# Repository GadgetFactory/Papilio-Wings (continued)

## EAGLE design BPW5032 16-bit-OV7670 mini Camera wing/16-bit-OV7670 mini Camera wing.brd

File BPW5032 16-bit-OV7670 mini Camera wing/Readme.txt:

BPW5032 OV7670 Camera Wing Manufacturing Package - Current Version 1.0

Special assembly instructions:
-Use RED for the PCB color.

CHANGELOG
8/22/2014 Version 1.0

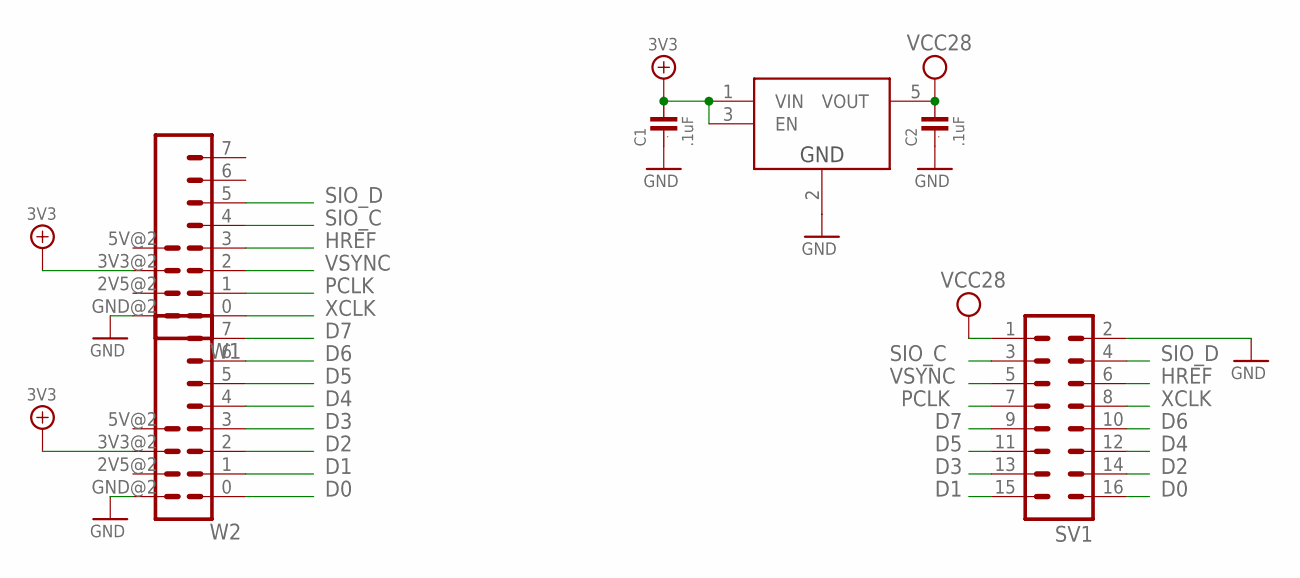
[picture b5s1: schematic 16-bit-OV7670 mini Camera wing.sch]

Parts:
C1, C2: .1uF; 0603; PARTNO GRM188F51E104ZA01D
SV1: ML16; PARTNO PRPC004DAAN-RC
U1: TPS73028; SOT23-DBV; PARTNO TPS73028DBVT
W1, W2: WING8WING8_NOHOLES; WINGSIDE_8BIT_NOHOLES; PARTNO 68001-112HLF

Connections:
3V3: C1.2, U1.1 (VIN), U1.3 (EN), W1.3V3@2 (3V3), W2.3V3@2 (3V3)
D0: SV1.16, W2.0 (1)
D1: SV1.15, W2.1 (2)
D2: SV1.14, W2.2 (3)
D3: SV1.13, W2.3 (4)
D4: SV1.12, W2.4 (5)
D5: SV1.11, W2.5 (6)
D6: SV1.10, W2.6 (7)
D7: SV1.9, W2.7 (8)
GND: C1.1, C2.1, SV1.2, U1.2 (GND), W1.GND@2 (GND), W2.GND@2 (GND)
HREF: SV1.6, W1.3 (4)
PCLK: SV1.7, W1.1 (2)
SIO_C: SV1.3, W1.4 (5)
SIO_D: SV1.4, W1.5 (6)
VCC28: C2.2, SV1.1, U1.5 (VOUT)
VSYNC: SV1.5, W1.2 (3)
XCLK: SV1.8, W1.0 (1)

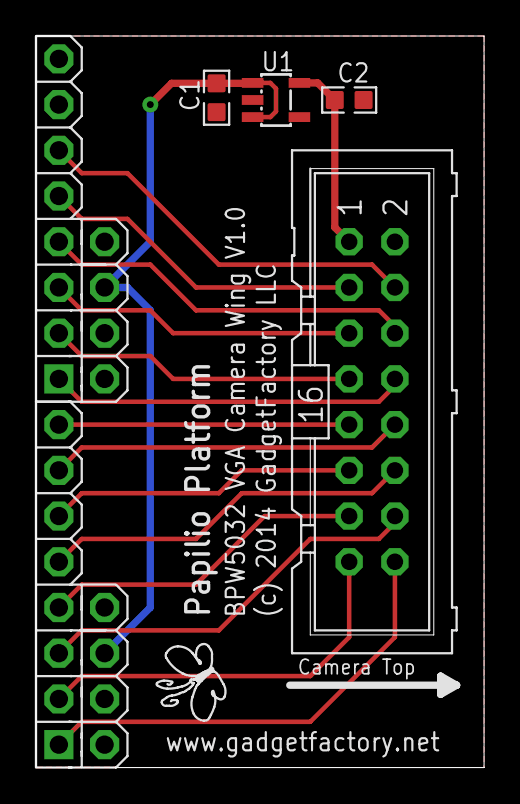
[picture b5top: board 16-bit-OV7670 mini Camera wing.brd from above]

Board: 2 copper layers, 24.9 x 40.6 mm, 7 parts (0 on the bottom side), 17 nets.

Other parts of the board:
U$1: BUTTERFLY_LOGO

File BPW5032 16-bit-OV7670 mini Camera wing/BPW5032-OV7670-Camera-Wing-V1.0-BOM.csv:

Qty-1,Part References,Value,Package,Mfg Part Num,Mfg Name,VID,Vendor Part Num,Description,Pkg Code,XREF
1,"SV1",,ML16,PRPC004DAAN-RC,Sullins Connector,DK,S2011EC-04-ND,CONN HEADER .100"" DUAL STR 8POS,ML16,REF194
2,"C1, C2",.1uF,0603,GRM188F51E104ZA01D,MURATA ELECTRONICS (VA),DK,490-1575-1-ND,CAP CER .1UF 25V Y5V 0603,603,REF96
1,"U1",TPS73028,SOT23-DBV,TPS73028DBVT,Texas Instruments,DK,296-18063-1-ND,IC REG LDO 2.8V 0.2A SOT23-5,SOT23-DBV,REF195
2,"W1, W2",WING8WING8_NOHOLES,WINGSIDE_8BIT_NOHOLES,68001-112HLF,FCI,DK,609-3275-ND,Papilio 8-bit Wing header. 12 Male Pin Headers to be split into 8 pins and 4 pins.,WINGSIDE_8BIT_NOHOLES,REF193

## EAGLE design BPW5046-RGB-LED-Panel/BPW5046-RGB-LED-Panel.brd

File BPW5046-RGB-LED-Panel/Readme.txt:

BPW5046 RGB LED Panel Wing Manufacturing Package - Current Version 1.1

Special assembly instructions:
-Use RED for the PCB color.

CHANGELOG
8/21/2014 Version 1.1

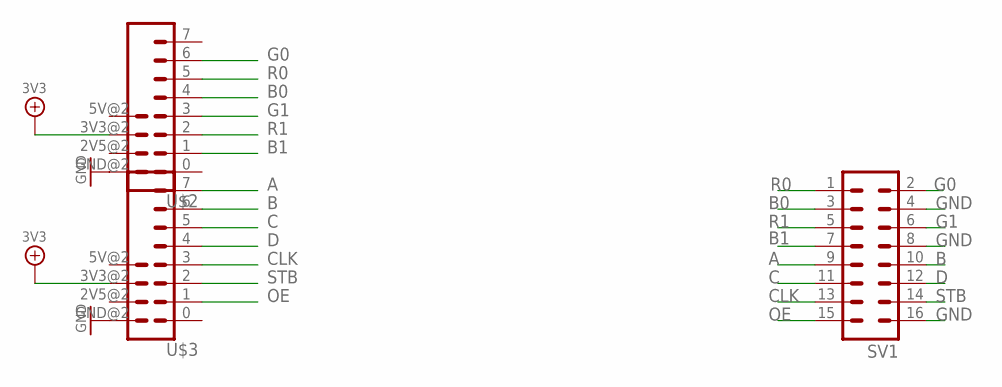
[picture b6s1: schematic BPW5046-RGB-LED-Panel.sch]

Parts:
SV1: ML16; PARTNO PRPC004DAAN-RC
U$2, U$3: WING8WING8_NOHOLES; WINGSIDE_8BIT_NOHOLES; PARTNO 68001-112HLF

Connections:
3V3: U$2.3V3@2 (3V3), U$3.3V3@2 (3V3)
A: SV1.9, U$3.7 (8)
B: SV1.10, U$3.6 (7)
B0: SV1.3, U$2.4 (5)
B1: SV1.7, U$2.1 (2)
C: SV1.11, U$3.5 (6)
CLK: SV1.13, U$3.3 (4)
D: SV1.12, U$3.4 (5)
G0: SV1.2, U$2.6 (7)
G1: SV1.6, U$2.3 (4)
GND: SV1.4, SV1.8, SV1.16, U$2.GND@2 (GND), U$3.GND@2 (GND)
OE: SV1.15, U$3.1 (2)
R0: SV1.1, U$2.5 (6)
R1: SV1.5, U$2.2 (3)
STB: SV1.14, U$3.2 (3)

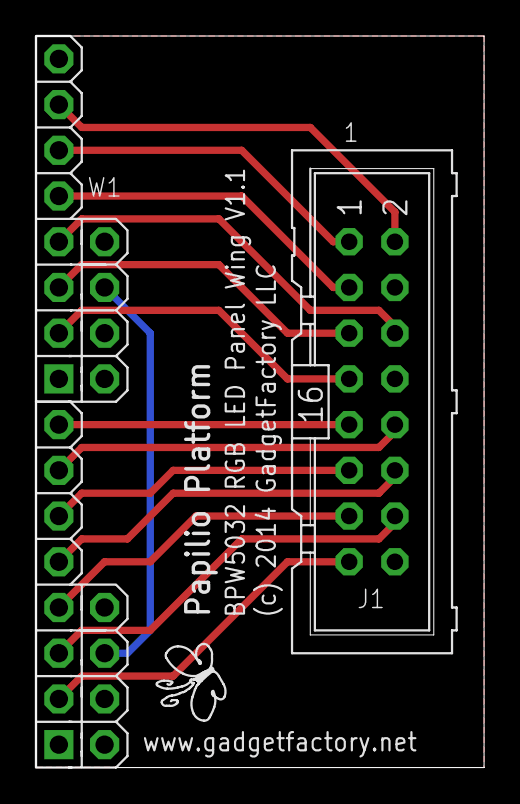
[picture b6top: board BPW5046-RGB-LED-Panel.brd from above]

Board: 2 copper layers, 24.9 x 40.6 mm, 4 parts (0 on the bottom side), 15 nets.

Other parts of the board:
U$1: BUTTERFLY_LOGO

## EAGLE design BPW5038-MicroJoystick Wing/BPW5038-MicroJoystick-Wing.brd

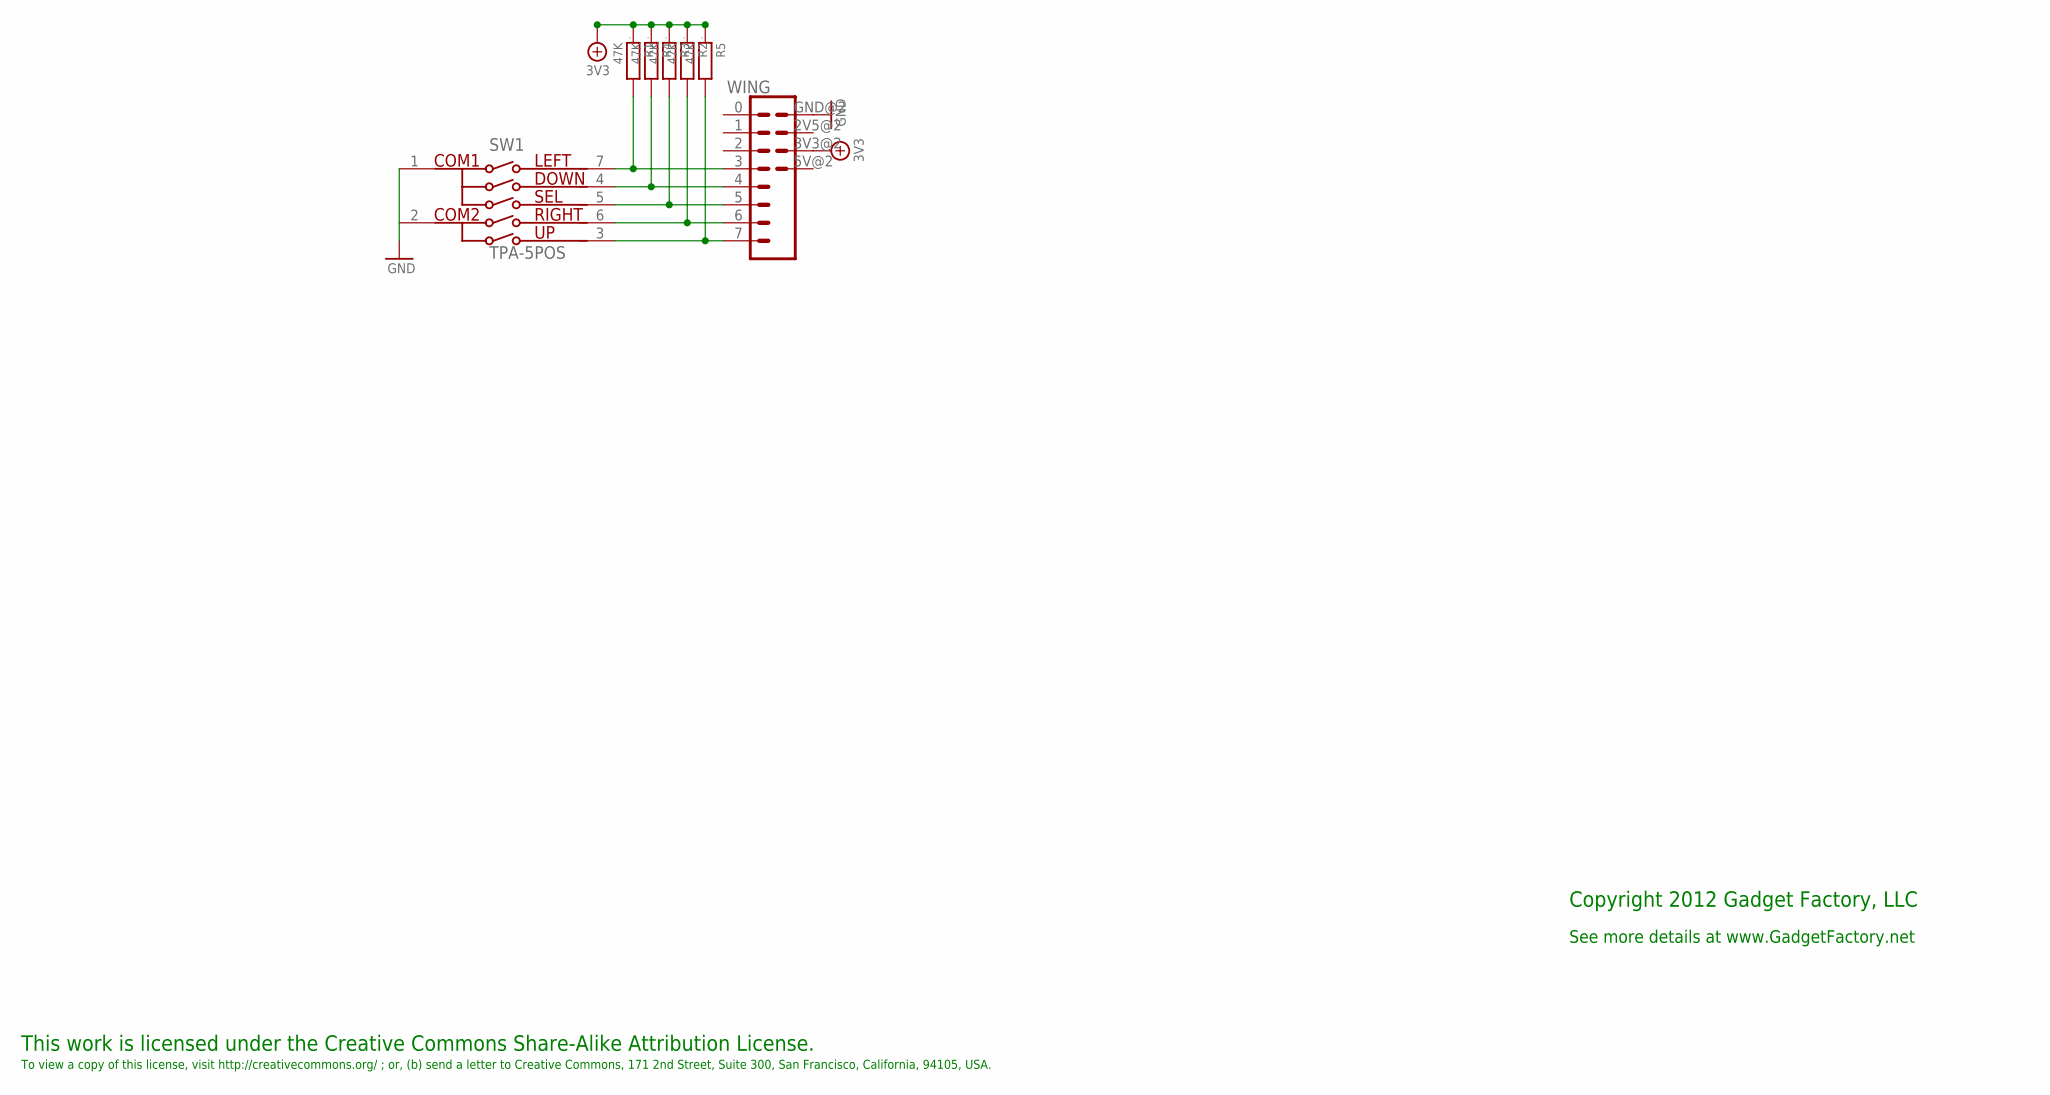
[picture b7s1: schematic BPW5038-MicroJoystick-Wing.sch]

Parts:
LOGO1: BUTTERFLY_LOGO
R1, R2, R3, R4, R5: 47K; 0603
SW1: TPA-5POS
WING: WING8; WINGSIDE_8BIT

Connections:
3V3: R1.1, R2.1, R3.1, R4.1, R5.1, WING.3V3@2 (3V3)
GND: SW1.1 (COM1), SW1.2 (COM2), WING.GND@2 (GND)
unnamed: R4.2, SW1.4 (DOWN), WING.4 (5)
unnamed: R1.2, SW1.7 (LEFT), WING.3 (4)
unnamed: R2.2, SW1.6 (RIGHT), WING.6 (7)
unnamed: R3.2, SW1.5 (SELECT), WING.5 (6)
unnamed: R5.2, SW1.3 (UP), WING.7 (8)

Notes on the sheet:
This work is licensed under the Creative Commons Share-Alike Attribution License.
To view a copy of this license, visit http://creativecommons.org/ ; or, (b) send a letter to Creative Commons, 171 2nd Street, Suite 300, San Francisco, California, 94105, USA.
Copyright 2012 Gadget Factory, LLC
See more details at www.GadgetFactory.net

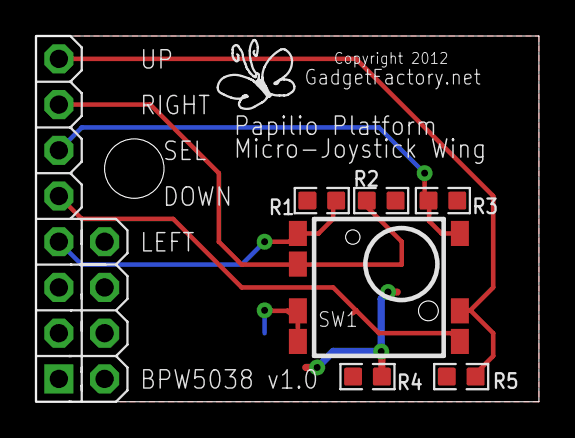
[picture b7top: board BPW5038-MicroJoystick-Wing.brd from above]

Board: 2 copper layers, 27.9 x 20.3 mm, 8 parts (0 on the bottom side), 7 nets.

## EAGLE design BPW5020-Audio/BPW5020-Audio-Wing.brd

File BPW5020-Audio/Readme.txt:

BPW5020 Audio Wing Manufacturing Package - Current Version 1.3

Special assembly instructions:
-Use RED for the PCB color.

CHANGELOG
8/21/2014 Version 1.3

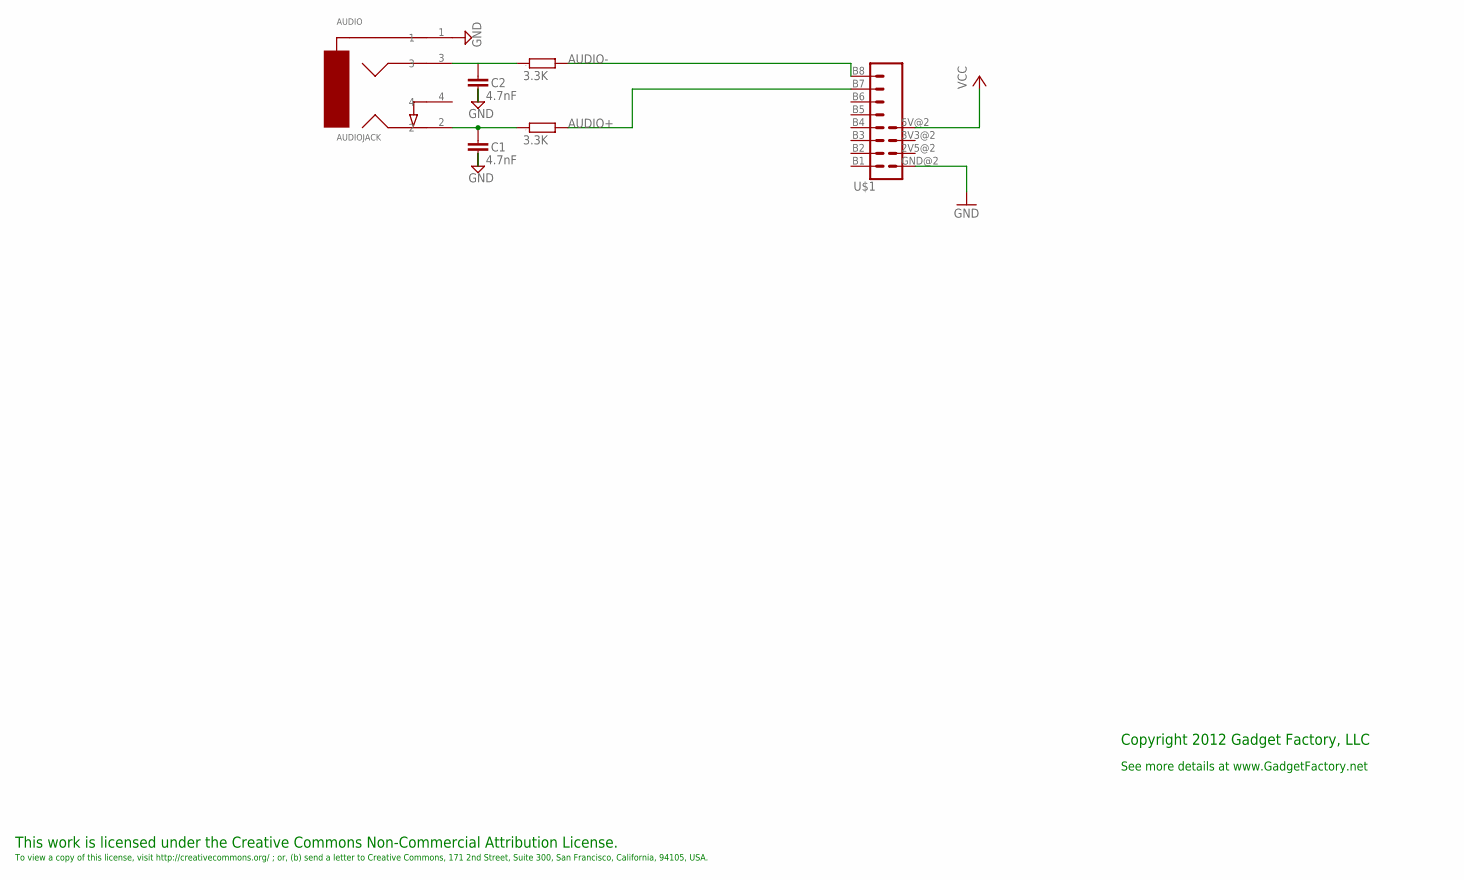
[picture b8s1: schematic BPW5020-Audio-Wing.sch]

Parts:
AUDIO: AUDIOJACK; AUDJCK
C1, C2: 4.7nF; C050-025X075
LOGO1: BUTTERFLY_LOGO
R1, R2: 3.3K; DUALRESISTOR
U$1: WING_8BIT; WINGSIDE_8BIT

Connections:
AUDIO+: R1.2, U$1.B7 (7)
AUDIO-: R2.2, U$1.B8 (8)
GND: AUDIO.1, C1.2, C2.2, U$1.GND@2 (GND)
unnamed: AUDIO.3, C2.1, R2.1
unnamed: AUDIO.2, C1.1, R1.1
VCC: U$1.5V@2 (5V)

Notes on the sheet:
This work is licensed under the Creative Commons Non-Commercial Attribution License.
To view a copy of this license, visit http://creativecommons.org/ ; or, (b) send a letter to Creative Commons, 171 2nd Street, Suite 300, San Francisco, California, 94105, USA.
Copyright 2012 Gadget Factory, LLC
See more details at www.GadgetFactory.net

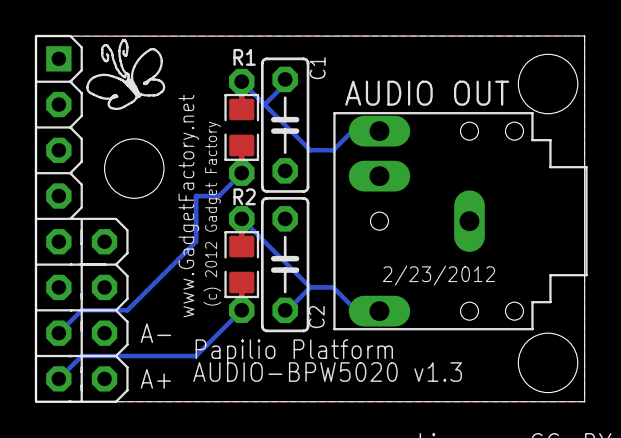
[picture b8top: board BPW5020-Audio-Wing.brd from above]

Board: 2 copper layers, 30.5 x 20.3 mm, 7 parts (0 on the bottom side), 5 nets.

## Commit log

2011-07-13 Initial version of TV-Video Wing.
2011-07-13 Updated design with bit 0 routed.
2011-07-13 Adding vhdl source files.
2011-07-14 Revision 1.0 of the Papilio Arcade MegaWing
2011-07-14 Updated resistor values.
2011-07-25 First revision
2011-07-27 PDF version of Schematic.
2011-07-28 Adding MicroSD Wing.
2011-07-28 Adding Several Wings at once.
2011-07-28 PDF's
2011-08-02 7 Segment Wing V1.0
2011-08-04 Updated Arcade MegaWing to support P1 and P/RAM footprints.
2012-01-30 Updated 8bit Wing Template
    -Wider drill holes
    -Fixed Dates
    -Fixed numbering
2012-02-08 LogiStart MegaWing Version 1.0
2012-02-08 PDF for LogiStart
2012-03-02 Checked in Mini Camera Wing
2012-04-04 Checking in MIDI Audio Wing design.
2012-04-04 Checking in assembly and schematic views of Midi Audio Wing.
2012-06-14 First cut at working out the placement of components for RetroCade MegaWing.
2012-06-27 Version 1.0 of the RetroCade MegaWing. Fully Routed
2012-07-02 Version 1.0 of the RetroCade Synth MegaWing!
2012-07-02 7/1/2012 Version 2.1 -Added Atari style joystick ports back, but with V-Score so they can be snapped off and replaced with other joystick types.
2012-08-01 16-bit Buffer Wing
    Version 1.2
2012-10-03 First revision of Dual Shield MegaWing
    Still needs 5V tolerant buffers.
2012-11-14 RetroCade Synth MegaWing 1.1
    8/21/2012 Version 1.1
    -Fixed placement of components under audio jacks.
    -Fixed 3.3V for Midi Out
    -Made holes for all connectors .04"
    -Made MIDI footprint support multiple parts.
2012-11-14 RetroCade PDF schematic
2012-12-19 LogicStart 2.1
    - activation of additional LEDs - colon in the middle (for clock
    display) and the apostrophe after the third digit (useful for displaying
    temperature as "°C") by way of adding the 5th digit select signal AN(4)
    - addition of a RGB LED
    - stereo audio instead of mono
    - support for Grove style sensor boards (analog only)
2012-12-23 New 16 Bit I/O Buffer design with 5V part.
2012-12-23 changelog
2012-12-28 Analog Wing
2012-12-28 Digital Wing
2012-12-28 Update Digital Wing to use Grove Connectors
2012-12-28 Add 5V resistors for Digital Grove Wing
2013-04-08 LogicStart MegaWing 2.1.1
    Adds buffer to RGB LED.
2014-06-09 Classic Computing Shield
2014-06-10 Rearrange with VGA on left
2014-06-10 Rearrange with VGA closer to pins
2014-06-10 Arcade MegaWing
2014-06-10 Move Serial port away from edge
2014-06-10 Housekeeping
2014-06-13 Major rework with all sections separated out.
2014-06-13 2nd Audio Jack, Mounting Holes
    Moved the Joystick ports to the same side, I'm considering rotating the
    whole thing 180 degrees so the joysticks are on the bottom...
    Added a second audio jack to the 16 bit Wing.
    The first audio jack is now connected to the Analog input pins of the
    atmel chip and also to FPGA pins. This is for reading data off tape
    drives or recording audio.
2014-06-17 Classic Computing Shield 1.0
2014-06-21 BPW5046 RGB LED Panel
2014-07-29 Added BOM for Classic Computing Shield V1.0
2014-07-29 Update BOM - Classic Computing Shield.
2014-08-12 LogicStart Shield V1.0
2014-08-15 Added GPIO Header
2014-08-21 Updated MicroSD card design
2014-08-21 gitignore
2014-08-21 SPI ADC
2014-08-21 IO Wing Update
2014-08-21 VGA Wing
2014-08-21 Audio Wing
2014-08-21 USB PHY
2014-08-21 Prototyping Wing
2014-08-21 USB FT232H Wing
2014-08-21 MicroJoystick Wing
2014-08-21 RGB LED Panel
2014-08-21 git ignore
2014-08-22 Buffer Wing
2014-08-22 OV7670 Camera Wing
2014-08-22 LogicStart Shield with Joystick generic header
2014-08-22 LogicStart Shield
2014-08-24 Move Joystick 2 on Classic Computing Shield
2014-08-24 LogicStart Shield 3D Model
2014-08-25 Added V-Score Dimension
2014-10-02 Stepper Controller
2014-10-02 Move J1 and J2 silkscreen
2014-10-20 Fix the PS/2 connectors.
2014-10-20 Rotated the Classic Computing Shield 180 degrees to make it more accessible.
2014-10-20 Classic Computing Shield V1.1
2014-10-22 LogicStart Shield V1.01
2014-10-22 Classic Computing Shield V1.01 - Disregard V1.1
    -Fixed the PS/2 footprints
    -Rotated the whole design 180 degrees to put the connectors at the top
    of the board and easier to work with.
    -Added Get Started URL
2015-01-18 Arcade MegaWing V1.3
2015-01-18 Fix Audio Jack.
